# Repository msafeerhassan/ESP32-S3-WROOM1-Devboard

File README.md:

# ESP32-S3-WROOM1-Devboard
A Custom ESP32-S3-WROOM1 N16R8 Development Board completely designed by me.

This project features raw ESP32-S3-WROOM1 N16R8 Chip to convert it into a professional development board. Several resistors are used along with capacitors for perfect circuit current flowing. 3 RGB colored LEDS are also placed on the PCB alongwith two Switch Push Buttons. A cool logo is placed on bottom right while text with each Pin is mentioned for ease of use in real life.

## Schematic Diagram:

## PCB:

### Made by Safeer Hassan

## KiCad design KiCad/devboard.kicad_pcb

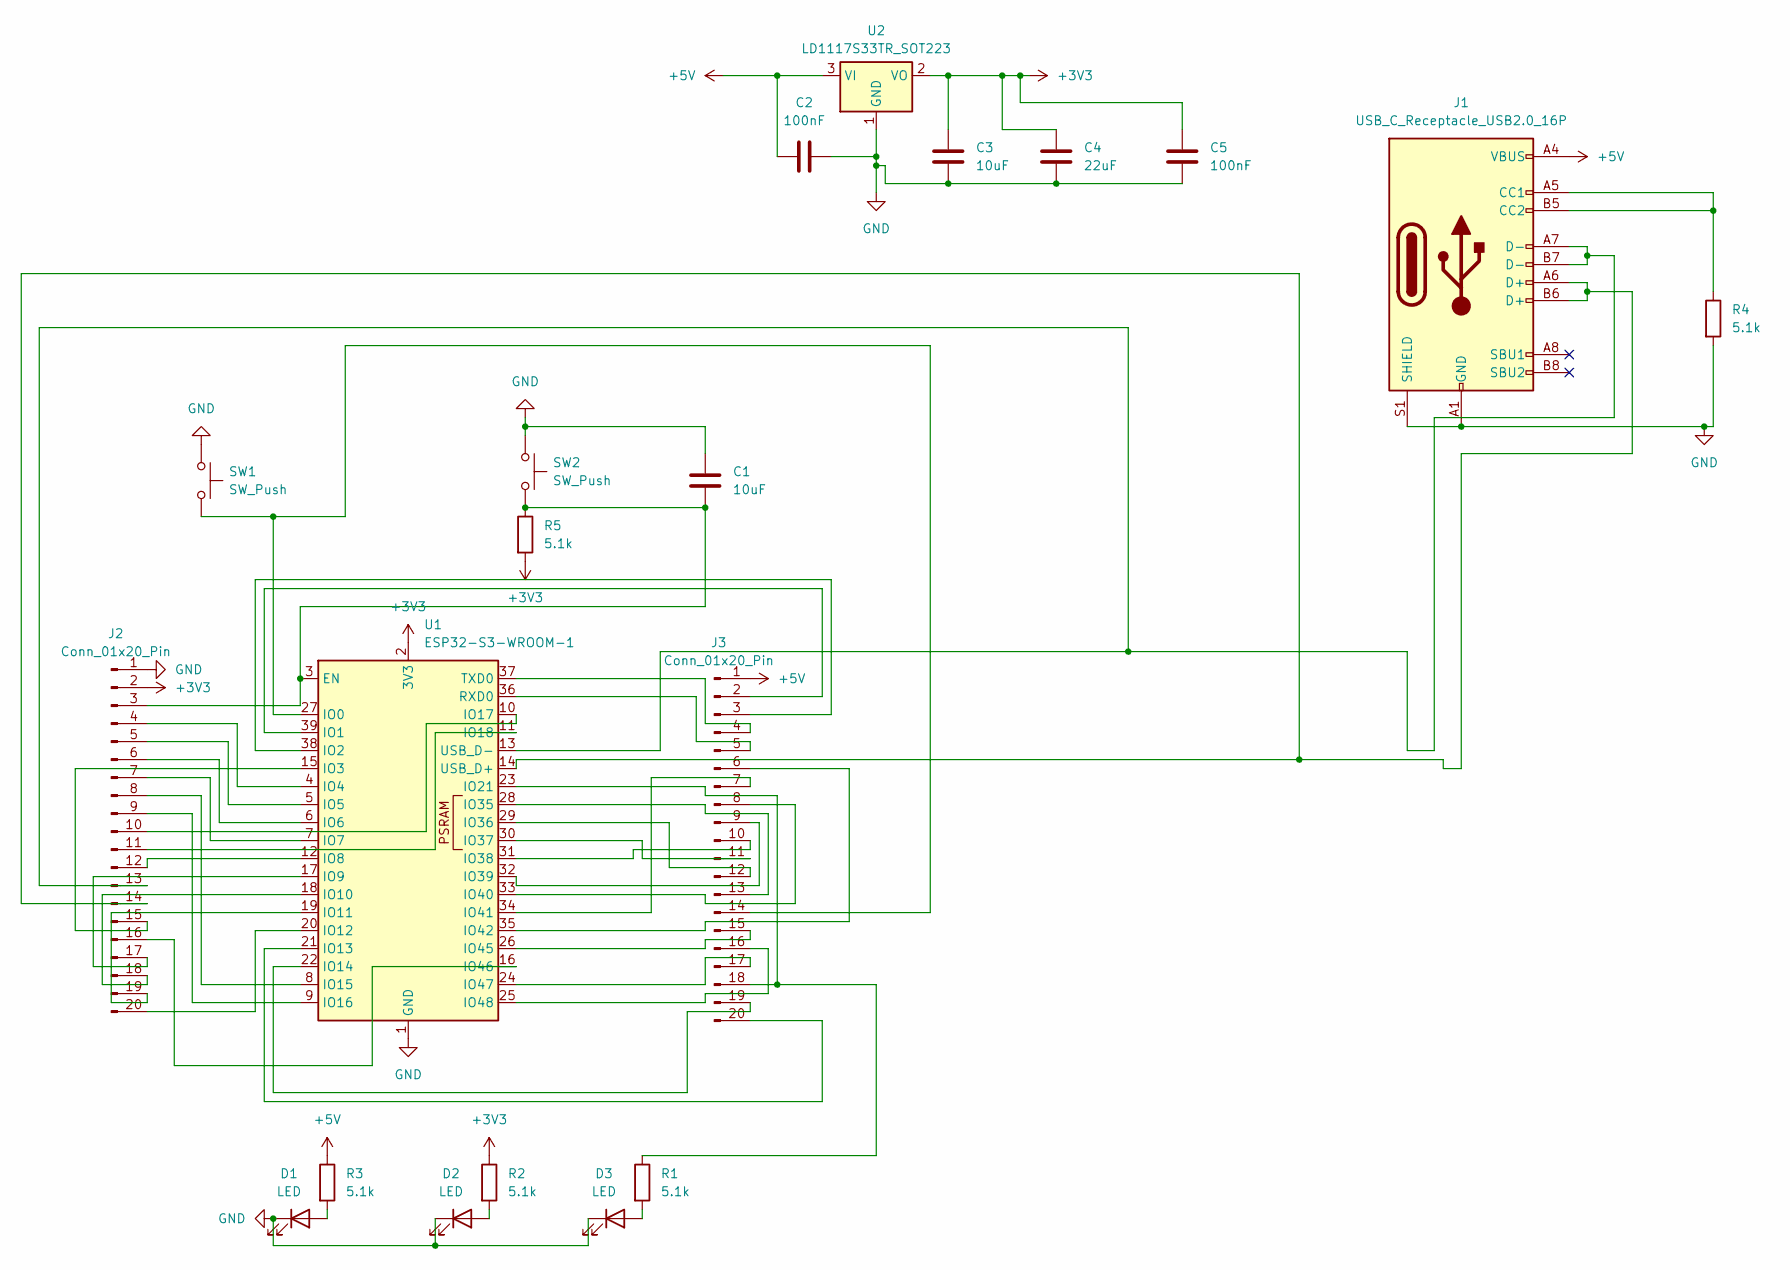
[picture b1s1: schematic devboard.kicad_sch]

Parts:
C1, C3: 10uF; C_1206_3216Metric_Pad1.33x1.80mm_HandSolder
C2, C5: 100nF; C_0603_1608Metric_Pad1.08x0.95mm_HandSolder
C4: 22uF; C_1206_3216Metric_Pad1.33x1.80mm_HandSolder
D1, D2, D3: LED; LED_0805_2012Metric_Pad1.15x1.40mm_HandSolder
J1: USB_C_Receptacle_USB2.0_16P; USB_C_Receptacle_HCTL_HC-TYPE-C-16P-01A
J2, J3: Conn_01x20_Pin; PinHeader_1x20_P2.00mm_Vertical
R1, R2, R3, R4, R5: 5.1k; R_0603_1608Metric_Pad0.98x0.95mm_HandSolder
SW1, SW2: SW_Push; SW_SPST_B3S-1000
U1: ESP32-S3-WROOM-1
U2: LD1117S33TR_SOT223; SOT-223-3_TabPin2

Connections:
+3V3: C3.1, C4.1, C5.1, J2.2, R2.1, R5.2, U1.2 (3V3), U2.2 (VO)
+5V: C2.1, J1.A4 (VBUS), J1.A9 (VBUS), J1.B4 (VBUS), J1.B9 (VBUS), J3.1, R3.1, U2.3 (VI)
GND: C1.1, C2.2, C3.2, C4.2, C5.2, D1.1 (K), D2.1 (K), D3.1 (K), J1.A1 (GND), J1.A12 (GND), J1.B1 (GND), J1.B12 (GND), J1.S1 (SHIELD), J2.1, R4.2, SW1.1, SW2.1, U1.1 (GND), U1.40 (GND), U1.41 (GND), U2.1 (GND)
unnamed: D1.2 (A), R3.2
unnamed: D2.2 (A), R2.2
unnamed: D3.2 (A), R1.2
unnamed: J1.A5 (CC1), J1.B5 (CC2), R4.1
unnamed: C1.2, J2.3, R5.1, SW2.2, U1.3 (EN)
unnamed: J2.4, U1.4 (IO4)
unnamed: J2.5, U1.5 (IO5)
unnamed: J2.6, U1.6 (IO6)
unnamed: J2.7, U1.7 (IO7)
unnamed: J2.8, U1.8 (IO15)
unnamed: J2.9, U1.9 (IO16)
unnamed: J2.10, U1.10 (IO17)
unnamed: J2.11, U1.11 (IO18)
unnamed: J2.12, U1.12 (IO8)
unnamed: J1.A7 (D-), J1.B7 (D-), J2.13, U1.13 (USB_D-)
unnamed: J1.A6 (D+), J1.B6 (D+), J2.14, U1.14 (USB_D+)
unnamed: J2.15, U1.15 (IO3)
unnamed: J2.16, U1.16 (IO46)
unnamed: J2.17, U1.17 (IO9)
unnamed: J2.18, U1.18 (IO10)
unnamed: J2.19, U1.19 (IO11)
unnamed: J2.20, U1.20 (IO12)
unnamed: J3.2, U1.39 (IO1)
unnamed: J3.3, U1.38 (IO2)
unnamed: J3.4, U1.37 (TXD0)
unnamed: J3.5, U1.36 (RXD0)
unnamed: J3.6, U1.35 (IO42)
unnamed: J3.7, U1.34 (IO41)
unnamed: J3.8, U1.33 (IO40)
unnamed: J3.9, U1.32 (IO39)
unnamed: J3.10, U1.31 (IO38)
unnamed: J3.11, U1.30 (IO37)
unnamed: J3.12, U1.29 (IO36)
unnamed: J3.13, U1.28 (IO35)
unnamed: J3.14, SW1.2, U1.27 (IO0)
unnamed: J3.15, U1.26 (IO45)
unnamed: J3.16, U1.25 (IO48)
unnamed: J3.17, U1.24 (IO47)
unnamed: J3.18, R1.1, U1.23 (IO21)
unnamed: J3.19, U1.22 (IO14)
unnamed: J3.20, U1.21 (IO13)

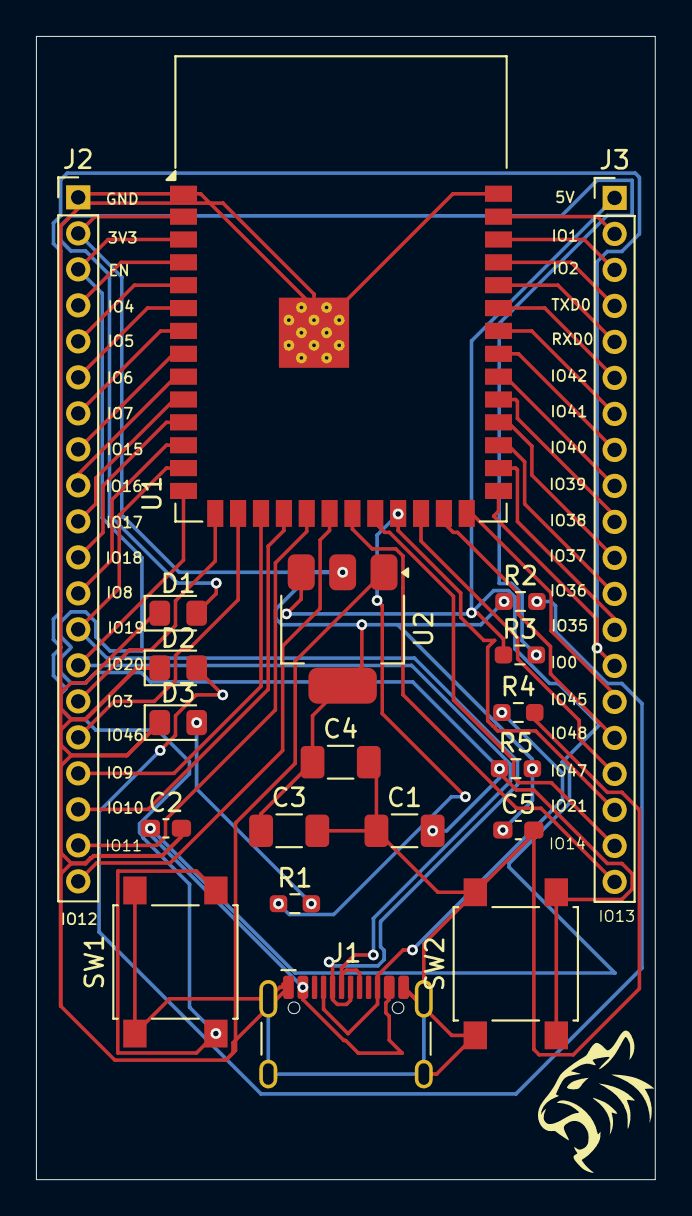
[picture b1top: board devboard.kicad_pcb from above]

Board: 2 copper layers, 34.4 x 63.5 mm, 20 parts (0 on the bottom side), 44 nets.

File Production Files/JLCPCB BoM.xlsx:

Comment | Designator | Footprint
10uf | C1,C3 | 1206
22uf | C4 | 1206
100nf | C2,C5 | 603
RED | D1 | 805
GREEN | D2 | 805
BLUE | D3 | 805
USB_C_Receptacle_USB2.0_16P | J1 | USB_C_Receptacle_HCTL_HC-TYPE-C-16P-01A
Conn_01x20_Pin | J2,J3 | PinHeader_1x20_P2.00mm_Vertical
5.1k | R1,R2,R3,R4,R5 | 603
SW_Push | SW1,SW2 | SW_SPST_B3S-1000
ESP32-S3-WROOM-1 | U1 | ESP32-S3-WROOM-1
LD1117S33TR_SOT223 | U2 | SOT-223-3_TabPin2

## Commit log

2026-01-14 Create r
2026-01-14 added KiCad files
2026-01-14 Create d
2026-01-14 uploaded production files
2026-01-14 Enhance README with detailed project information
    Expanded project description and added schematic and PCB images.
